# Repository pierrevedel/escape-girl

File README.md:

# ESCAPE GIRL - l'escape game sur la sensibilisation au harcelement sexuel

Escape girl est un outil pédagogique destiné à un public d'adolescents sous forme d'escape game inspiré d'une [campagne de communication gouvernementale de 2016](https://arretonslesviolences.gouv.fr/je-suis-professionnel/outils-de-communication) diffusée dans les transports en commun. Les affiches de cette campagne montrent le cheminement de pensée des 3 acteurs d'un harcèlement (l'auteur, la victime et le temoin) sous forme de plan de métro.
Le plateau de jeu pédagogique reprend le fond et la forme de cette campagne. Le jeune sensibilisé doit retrouver quel acteur pense quoi en repositionnant les étiquettes. Il n'y a qu'une seule combinaison qui affichera la clef complète de l'escape game (un chiffre qui permet de passer à l'étape d'après).

]

## clef affichée
La clef de ce enigme est un 5. le segment horizontal median s'affiche dès l'alimentaton du système. Ce plateau n'est qu'une enigme de l'escape complet. les autres enigmes donnent les chiffres 7 et 0 : 750€, le montant de l'amende pour agression. (on peut aussi proposer le 3020, numéro d'appel des élèves harcelés à l’école )

## contenu numérique
- un plateau de jeu (épaisseur 22mm) et des étiquettes (épaisseur 15mm) à usiner d'apres un modèle 3d (.step)
- une infographie à graver au laser d'apres un modèle vectoriel (.svg)
- un schéma électronique à cabler ou faire fabriquer le pcb à ouvrir avec kicad (.kicad_sch & .kicad_pcb)
- un couronne pour l'afficheur numérique à fabriquer sur imprimante 3d d'après modèle 3d (.stl)

## composants électroniques
la référence donné est celle du revendeur gotronic

| composant  | conditionnement | quantité | référence |
| ------ | ------ | ------ | ------ |
| Connecteurs sub-D mâles Droit 9 contacts | 1 | 12 | 08105 |
| Connecteurs sub-D femelle Droit 9 contacts | 1 | 12 | 08110 |
| vis tête fraisée inox M3 10 mm  | 10 | 3 | 11626 |
| ecrou M3  | 1 | 24 |  |
| Leds rouges LED5RL leds éco 5 mm | 10 | 1 | 03025 |
| Clip 5 mm 115SC neoprene | 1 | 4 | 03118 |
| Résistance carbone 1W 68Ω | 1 | 5| 04222 |
| Résistance carbone 1W 120Ω  | 1 | 1 | 04225 |
| Afficheur SC08-11R 20 mm rouge CC | 1 | 1 | 03176 |
| Platine à connecteur micro-USB B 2586 | 1 | 1 | 34786 |
| vis auto-taraudeuses 2,2x6,5mm  | 10 | 1 | 11850 |
| Inverseur à glissière miniature | 1 | 1 | ESP101 |
| Connecteur NSK254-4C mâle coudé 4 cts | 1 | 2 | 48712 |
| Boîtier NSK254-4B femelle pour 4 cts | 1 | 2 | 48722 |
| contact NSK254-0 pour boîtier NSK254 | 10 | 2 | 48724 |
| Assortiment FCS60 fil souple - 60 m  | 1 | 1 | 08956 |
| batterie avec cable micro USB-B (max 92x60x12mm) | 1 | 1 |  |

## outillage nécessaire
- fraiseuse à commande numérique
- laser à commande numérique
- pince à sertir necessaire pour les connecteurs NSK254
- pince à dénuder
- pince coupante
- poste à souder l'étain
- embout à chanfreiner que les vis à têtes fraisées affleurent la surface du tableau de bord
- pistolet à colle pour maintenir les cables
- scratch autocollant pour maintenir la batterie

## maître d'ouvrage
l'escape game complet est organisé par [aroeven occitanie](https://aroeven-occitanie.fr/)

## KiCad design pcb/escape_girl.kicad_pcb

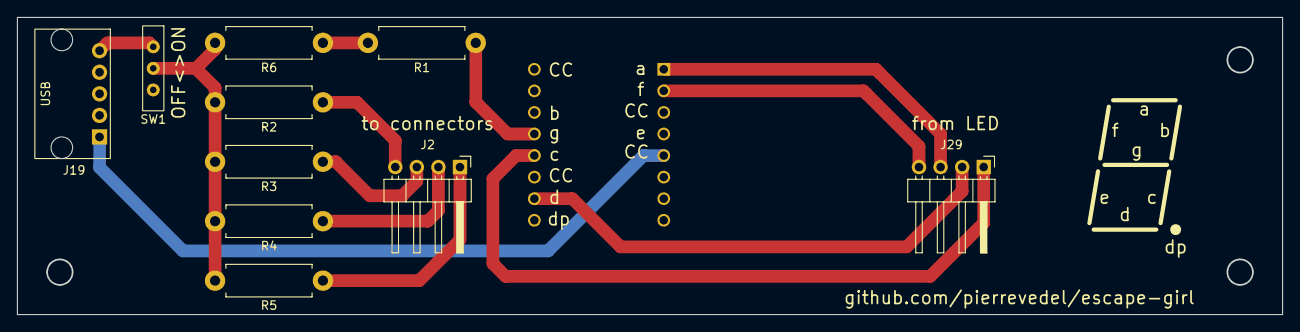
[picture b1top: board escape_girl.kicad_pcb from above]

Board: 2 copper layers, 149.0 x 35.0 mm, 11 parts (1 on the bottom side), 13 nets.

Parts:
DS1: SC08-11SRWA; SC08-11SRWA_DIPS1524W80P254L2770H865Q16N
J2, J29: Conn_01x04; PinHeader_1x04_P2.54mm_Horizontal
J19: USB_B_Micro; USB_micro-B_polulu-2586
R1: 120; R_Axial_DIN0411_L9.9mm_D3.6mm_P12.70mm_Horizontal
R2, R3, R4, R5, R6: 68; R_Axial_DIN0411_L9.9mm_D3.6mm_P12.70mm_Horizontal
SW1: SW_SPDT; SW_slide_SPDT_10x2.5mm

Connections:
+5V: J19.1 (VBUS), SW1.3 (C)
GND: DS1.5 (COMMON_CATHODE_2), J19.5 (GND)
unnamed: DS1.1 (ANODE_A), J29.3
unnamed: DS1.2 (ANODE_F), J29.4
unnamed: DS1.10 (ANODE_D), J29.2
unnamed: DS1.12 (ANODE_C), J29.1
unnamed: DS1.13 (ANODE_G), R1.1
unnamed: J2.1, R5.1
unnamed: J2.2, R4.1
unnamed: J2.3, R3.1
unnamed: J2.4, R2.1
unnamed: R1.2, R6.1
unnamed: R2.2, R3.2, R4.2, R5.2, R6.2, SW1.2 (B)

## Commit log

2023-03-16 1st up
